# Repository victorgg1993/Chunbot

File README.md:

# 春 Bot

## Este proyecto tiene dos bloques:

### Mando

- **3D**: modelos 3D del mando
- **Codigo**: Ejemplos de código para el mando
- **PCB**: Diseños de la placa

### Robot

- **3D**: modelos 3D del robot
- **Codigo**: Ejemplos de código para el robot
- **PCB**: Diseños de la placa

## Instalación de dispositivos:

En Linux es necesario añadir los dispositivos en una whitelist en _/etc/udev/rules.d_. Se recomienda seguir la instalación oficial ya que las nuevas versiones de la IDE de Arduino lo gestionan de forma automática.

Link: https://docs.arduino.cc/software/ide-v2/tutorials/getting-started/ide-v2-downloading-and-installing/

---

## Instalación de las librerías:

Una vez se abra el menú, cargar las librerías que se encuentran en este proyecto.
La carpeta donde se encuentran las librerías a instalar es "LibreriasArduino".

---

## Elegir microcontrolador:

La flecha roja muestra en todo momento qué placa tenemos seleccionada, la verde indica qué puerto USB será usado para programar el microcontrolador.

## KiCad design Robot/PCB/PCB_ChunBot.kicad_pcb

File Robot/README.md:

# 春 Bot

## Contenido:

- PCB: Diseño de la PCB, tanto esquemáticos como la propia PCB ( Kicad )
- 3D: Modelos 3D ( FreeCAD )
- Codigo: Contiene códigos de ejemplo ( Arduino Mega 2560 )

## Pines:

|     Uso      | Pin |                                  Uso                                  |
| :----------: | :-: | :-------------------------------------------------------------------: |
|    Faros     | A14 |      Controla un mosfet que enciende y apaga los focos frontales      |
|              |     |                                                                       |
| Temperatura  | A15 |              Sensor de temperatura. Acepta TMP36 y LM35               |
|              |     |                                                                       |
|  Pulsadores  | A8  |                            Pulsador abajo                             |
|  Pulsadores  | A9  |                           Pulsador derecha                            |
|  Pulsadores  | A10 |                          Pulsador central/ok                          |
|  Pulsadores  | A11 |                          Pulsador izquierda                           |
|  Pulsadores  | A12 |                            Pulsador arriba                            |
|              |     |                                                                       |
|    Radio     | D18 |    Módulo radio NRF24L01, pin de interrupción. ( no implementado )    |
|    Radio     | D50 |                  Módulo radio NRF24L01, pin SPI MISO                  |
|    Radio     | D51 |                  Módulo radio NRF24L01, pin SPI MOSI                  |
|    Radio     | D52 |                  Módulo radio NRF24L01, pin SPI SCK                   |
|    Radio     | D53 |                  Módulo radio NRF24L01, pin SPI #CNS                  |
|    Radio     | D43 |                   Módulo radio NRF24L01, pin SPI CE                   |
|              |     |                                                                       |
| Siguelíneas  | D23 |           Sensor izquierdo exterior del seguidor de líneas            |
| Siguelíneas  | D41 |           Sensor izquierdo interior del seguidor de líneas            |
| Siguelíneas  | D42 |            Sensor derecho exterior del seguidor de líneas             |
| Siguelíneas  | D45 |            Sensor derecho interior del seguidor de líneas             |
|              |     |                                                                       |
| Display16x2  | D33 |                        Data 4 ( bus de datos )                        |
| Display16x2  | D35 |                        Data 5 ( bus de datos )                        |
| Display16x2  | D37 |                        Data 6 ( bus de datos )                        |
| Display16x2  | D39 |                        Data 7 ( bus de datos )                        |
| Display16x2  | D31 |                                Enable                                 |
| Display16x2  | D29 |                                  RS                                   |
| Display16x2  | D27 |      Controla un mosfet que enciende y apaga la luz del display       |
|              |     |                                                                       |
| Display7seg  | D17 |                              Segmento A                               |
| Display7seg  | D25 |                              Segmento B                               |
| Display7seg  | D16 |                              Segmento C                               |
| Display7seg  | D15 |                              Segmento D                               |
| Display7seg  | D14 |                              Segmento E                               |
| Display7seg  | D22 |                              Segmento F                               |
| Display7seg  | D24 |                              Segmento G                               |
|              |     |                                                                       |
|     OLED     | D20 |                   SDA, bus I2C de la pantalla OLED                    |
|     OLED     | D21 |                   SCL, bus I2C de la pantalla OLED                    |
|              |     |                                                                       |
|    Servos    | D8  |               Servo izquierdo. Usa PWM para su control                |
|    Servos    | D12 |                Servo derecho. Usa PWM para su control                 |
|    Servos    | D6  |                Servo extra 1. Usa PWM para su control                 |
|    Servos    | D7  |                Servo extra 2. Usa PWM para su control                 |
|    Servos    | D9  |                Servo extra 3. Usa PWM para su control                 |
|    Servos    | D10 |                Servo extra 4. Usa PWM para su control                 |
|    Servos    | D11 |                Servo extra 5. Usa PWM para su control                 |
|              |     |                                                                       |
|   Zumbador   | D5  |              Control vía PWM del zumbador piezoeléctrico              |
|              |     |                                                                       |
|   Mando TV   | D4  |     Sensor infrarrojo para el mando de TV. Usa el protocolo NEC32     |
|              |     |                                                                       |
| Ultrasonidos | D3  |          Emite una señal de eco que rebota contra el objeto           |
| Ultrasonidos | D2  | Recibe la señal de eco emitida por el otro pin ( usa interrupciones ) |
|              |     |                                                                       |

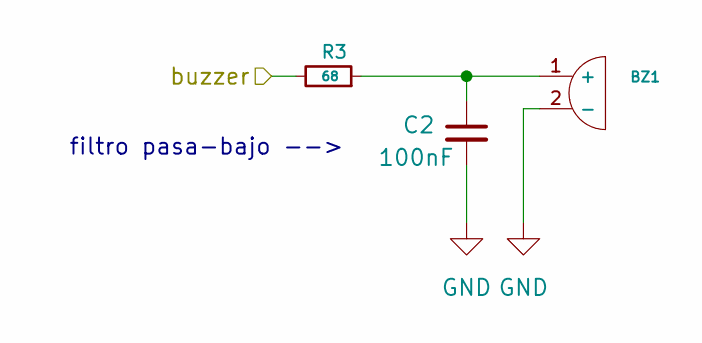
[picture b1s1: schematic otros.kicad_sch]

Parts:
BZ1: Buzzer_12x9.5RM7.6
C2: 100nF; C_0805_2012Metric_Pad1.18x1.45mm_HandSolder
R3: 68; R_0805_2012Metric

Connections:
GND: BZ1.2 (-), C2.2; also elsewhere on the board
unnamed: BZ1.1 (+), C2.1, R3.1
buzzer: R3.2; also elsewhere on the board

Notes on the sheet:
filtro pasa-bajo -->

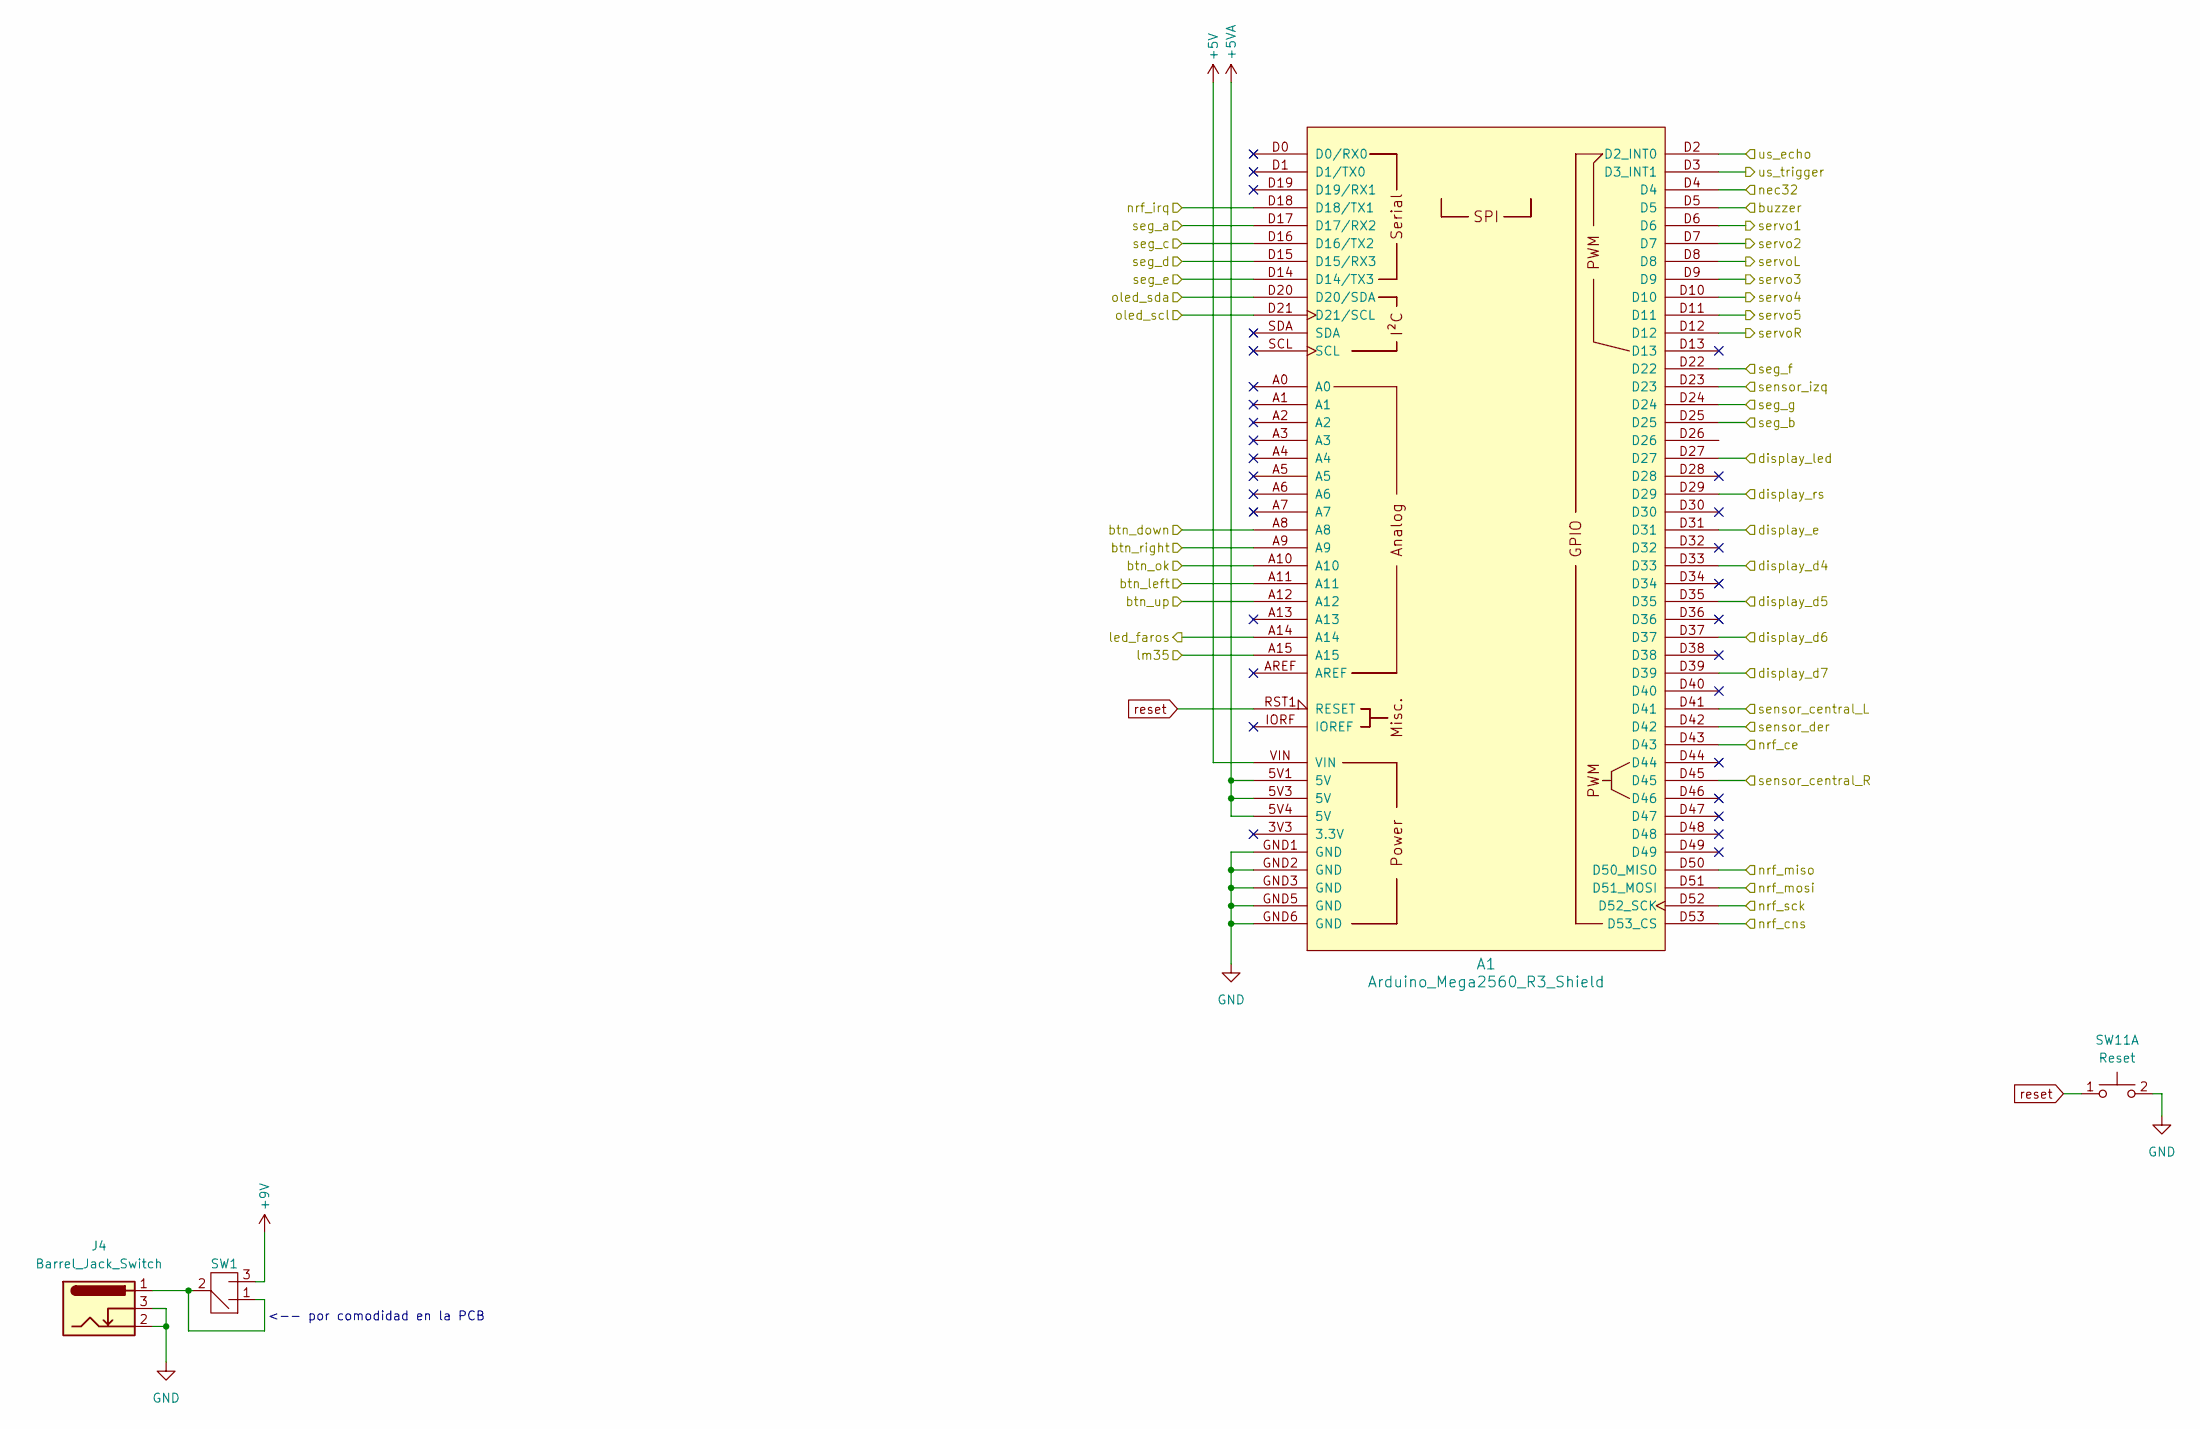
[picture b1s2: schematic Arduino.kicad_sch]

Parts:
A1: Arduino_Mega2560_R3_Shield
J4: Barrel_Jack_Switch; POWER_JACK_SLOT
SW1: SS12D10
SW11: Reset; SW_PUSH_6mm_H5mm

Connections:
+5V: A1.VIN; also elsewhere on the board
+5VA: A1.5V1 (5V), A1.5V3 (5V), A1.5V4 (5V); also elsewhere on the board
+9V: SW1.3; also elsewhere on the board
GND: A1.GND1 (GND), A1.GND2 (GND), A1.GND3 (GND), A1.GND5 (GND), A1.GND6 (GND), J4.2, J4.3, SW11.2 (D); also elsewhere on the board
unnamed: J4.1, SW1.1, SW1.2
btn_down: A1.A8; also elsewhere on the board
btn_left: A1.A11; also elsewhere on the board
btn_ok: A1.A10; also elsewhere on the board
btn_right: A1.A9; also elsewhere on the board
btn_up: A1.A12; also elsewhere on the board
buzzer: A1.D5; also elsewhere on the board
display_d4: A1.D33; also elsewhere on the board
display_d5: A1.D35; also elsewhere on the board
display_d6: A1.D37; also elsewhere on the board
display_d7: A1.D39; also elsewhere on the board
display_e: A1.D31; also elsewhere on the board
display_led: A1.D27; also elsewhere on the board
display_rs: A1.D29; also elsewhere on the board
led_faro: A1.A14; also elsewhere on the board
lm35: A1.A15; also elsewhere on the board
nec32: A1.D4; also elsewhere on the board
nrf_ce: A1.D43; also elsewhere on the board
nrf_cns: A1.D53 (D53_CS); also elsewhere on the board
nrf_irq: A1.D18 (D18/TX1); also elsewhere on the board
nrf_miso: A1.D50 (D50_MISO); also elsewhere on the board
nrf_mosi: A1.D51 (D51_MOSI); also elsewhere on the board
nrf_sck: A1.D52 (D52_SCK); also elsewhere on the board
oled_scl: A1.D21 (D21/SCL); also elsewhere on the board
oled_sda: A1.D20 (D20/SDA); also elsewhere on the board
reset: A1.RST1 (RESET), SW11.1 (C)
seg_a: A1.D17 (D17/RX2); also elsewhere on the board
seg_b: A1.D25; also elsewhere on the board
seg_c: A1.D16 (D16/TX2); also elsewhere on the board
seg_d: A1.D15 (D15/RX3); also elsewhere on the board
seg_e: A1.D14 (D14/TX3); also elsewhere on the board
seg_f: A1.D22; also elsewhere on the board
seg_g: A1.D24; also elsewhere on the board
sensor_central_L: A1.D41; also elsewhere on the board
sensor_central_R: A1.D45; also elsewhere on the board
sensor_der: A1.D42; also elsewhere on the board
sensor_izq: A1.D23; also elsewhere on the board
servo 1: A1.D6; also elsewhere on the board
servo 2: A1.D7; also elsewhere on the board
servo 3: A1.D9; also elsewhere on the board
servo 4: A1.D10; also elsewhere on the board
servo 5: A1.D11; also elsewhere on the board
servoL: A1.D8; also elsewhere on the board
servoR: A1.D12; also elsewhere on the board
ultrasonidos_echo: A1.D2 (D2_INT0); also elsewhere on the board
ultrasonidos_trigger: A1.D3 (D3_INT1); also elsewhere on the board

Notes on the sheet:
<-- por comodidad en la PCB

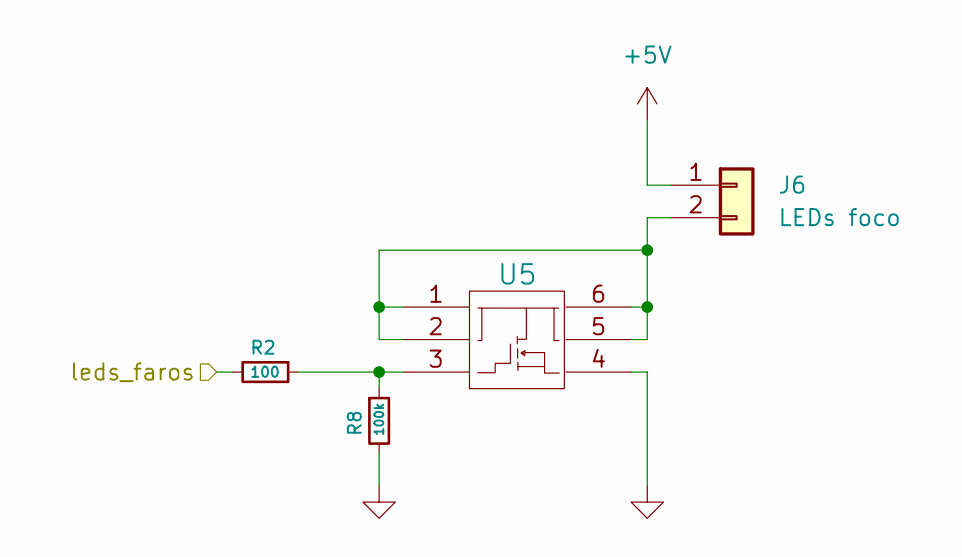
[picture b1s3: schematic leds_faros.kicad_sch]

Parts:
J6: LEDs foco; XH2.54_2Pin
R2: 100; R_0805_2012Metric
R8: 100k; R_0805_2012Metric
U5: SQ3456BEV; TSOP-6_1.65x3.05mm_P0.95mm

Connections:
+5V: J6.1; also elsewhere on the board
GND: R8.2, U5.4; also elsewhere on the board
unnamed: J6.2, U5.1, U5.2, U5.5, U5.6
unnamed: R2.1, R8.1, U5.3
led_faro: R2.2; also elsewhere on the board

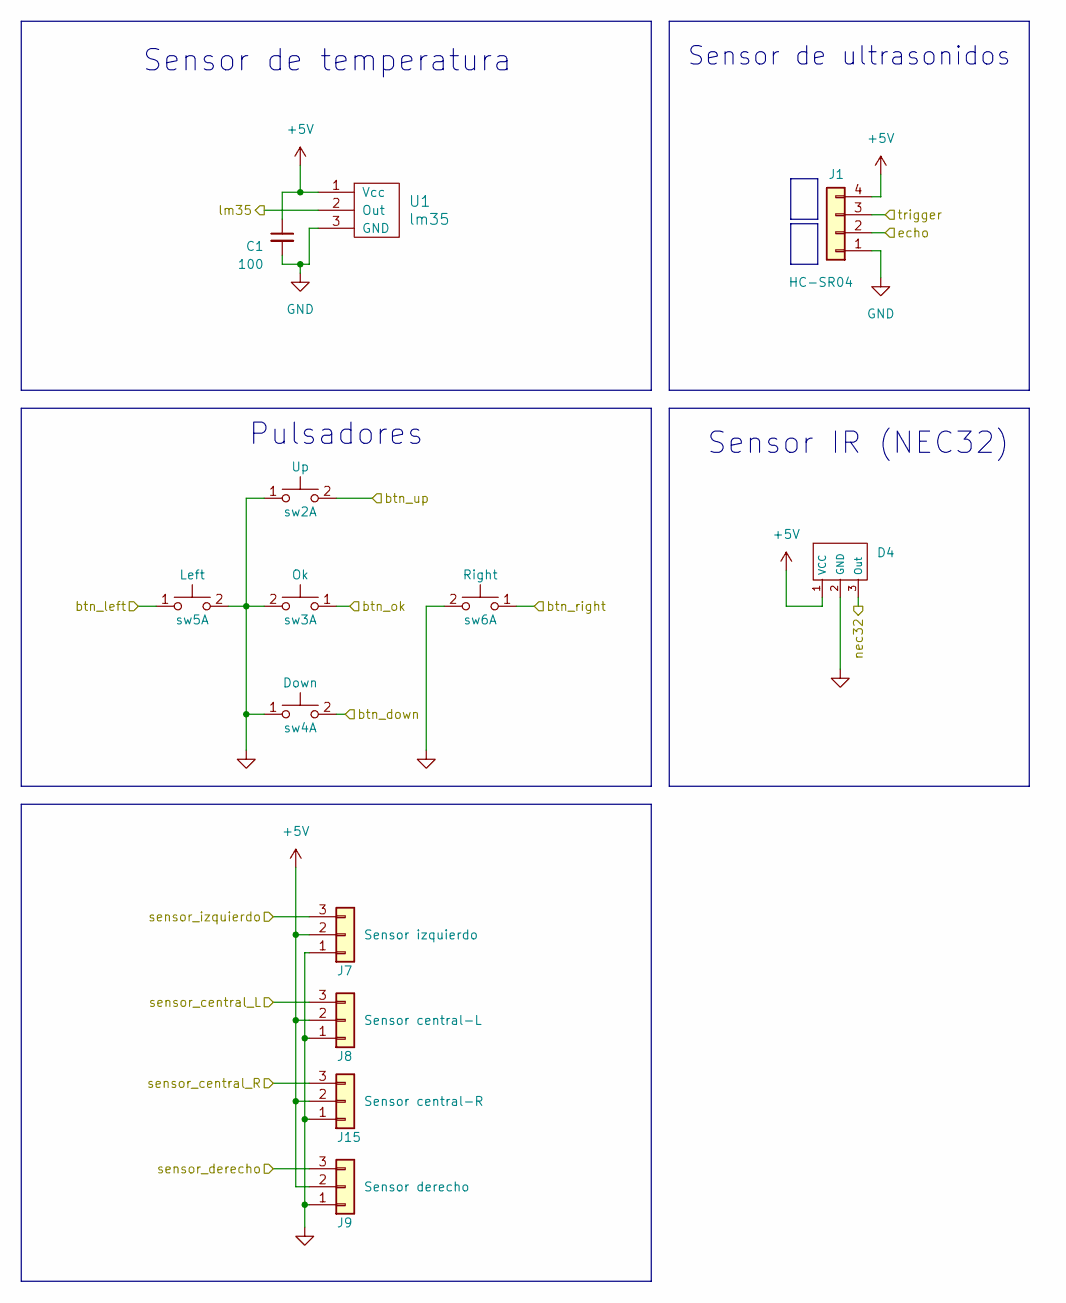
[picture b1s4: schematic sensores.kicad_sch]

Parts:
C1: 100; C_0805_2012Metric
D4: VS1838
J1: HC-SR04
J7: Sensor izquierdo; PinHeader_1x03_P2.54mm_Vertical
J8: Sensor central-L; PinHeader_1x03_P2.54mm_Vertical
J9: Sensor derecho; PinHeader_1x03_P2.54mm_Vertical
J15: Sensor central-R; PinHeader_1x03_P2.54mm_Vertical
U1: lm35; TO-92L_Inline_Wide
sw2: Up; SW_Push_1P1T_NO_CK_KSC7xxJ
sw3: Ok; SW_Push_1P1T_NO_CK_KSC7xxJ
sw4: Down; SW_Push_1P1T_NO_CK_KSC7xxJ
sw5: Left; SW_Push_1P1T_NO_CK_KSC7xxJ
sw6: Right; SW_Push_1P1T_NO_CK_KSC7xxJ

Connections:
+5V: C1.1, D4.1 (VCC), J1.4, J7.2, J8.2, J9.2, J15.2, U1.1 (Vcc); also elsewhere on the board
GND: C1.2, D4.2 (GND), J1.1, J7.1, J8.1, J9.1, J15.1, U1.3 (GND), sw2.1 (C), sw3.2 (D), sw4.1 (C), sw5.2 (D), sw6.2 (D); also elsewhere on the board
btn_down: sw4.2 (D); also elsewhere on the board
btn_left: sw5.1 (C); also elsewhere on the board
btn_ok: sw3.1 (C); also elsewhere on the board
btn_right: sw6.1 (C); also elsewhere on the board
btn_up: sw2.2 (D); also elsewhere on the board
lm35: U1.2 (Out); also elsewhere on the board
nec32: D4.3 (Out); also elsewhere on the board
sensor_central_L: J8.3; also elsewhere on the board
sensor_central_R: J15.3; also elsewhere on the board
sensor_der: J9.3; also elsewhere on the board
sensor_izq: J7.3; also elsewhere on the board
ultrasonidos_echo: J1.2; also elsewhere on the board
ultrasonidos_trigger: J1.3; also elsewhere on the board

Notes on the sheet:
Sensor IR (NEC32)
Sensor de ultrasonidos
Sensor de temperatura
Pulsadores

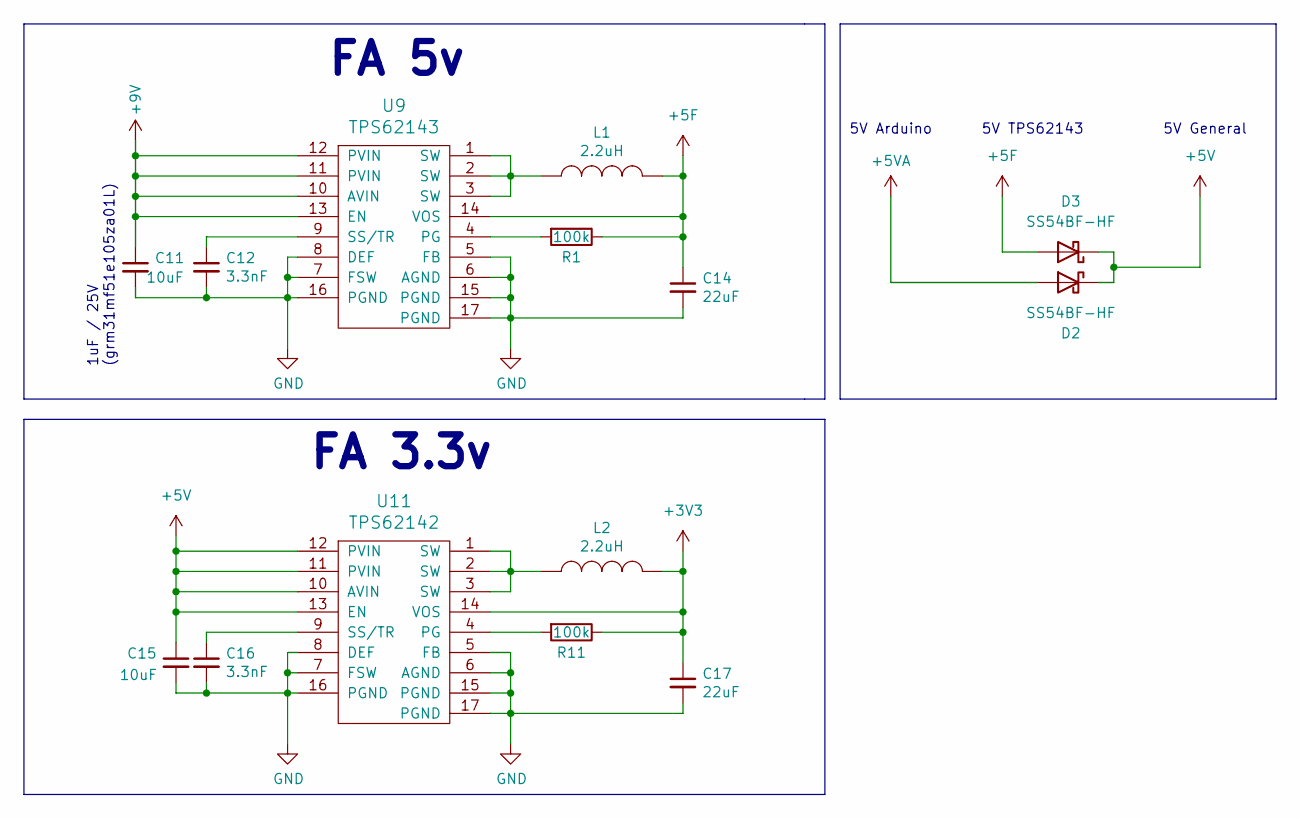
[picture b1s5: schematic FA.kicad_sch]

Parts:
C11: 10uF; C_1206_3216Metric_Pad1.33x1.80mm_HandSolder
C12, C16: 3.3nF; C_0805_2012Metric_Pad1.18x1.45mm_HandSolder
C14, C17: 22uF; C_0805_2012Metric_Pad1.18x1.45mm_HandSolder
C15: 10uF; C_0805_2012Metric_Pad1.18x1.45mm_HandSolder
D2, D3: SS54BF-HF; D_SMB_Handsoldering
L1, L2: 2.2uH; L_Taiyo-Yuden_NR-50xx_HandSoldering
R1, R11: 100k; R_0805_2012Metric_Pad1.20x1.40mm_HandSolder
U9: TPS62143; QFN-16-1EP_3x3mm_P0.5mm_EP1.7x1.7mm
U11: TPS62142; QFN-16-1EP_3x3mm_P0.5mm_EP1.7x1.7mm

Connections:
+3V3: C17.1, L2.2, R11.1, U11.14 (VOS); also elsewhere on the board
+5F: C14.1, D3.2 (A), L1.2, R1.1, U9.14 (VOS)
+5V: C15.1, D2.1 (K), D3.1 (K), U11.10 (AVIN), U11.11 (PVIN), U11.12 (PVIN), U11.13 (EN); also elsewhere on the board
+5VA: D2.2 (A); also elsewhere on the board
+9V: C11.1, U9.10 (AVIN), U9.11 (PVIN), U9.12 (PVIN), U9.13 (EN); also elsewhere on the board
GND: C11.2, C12.2, C14.2, C15.2, C16.2, C17.2, U9.5 (FB), U9.6 (AGND), U9.7 (FSW), U9.8 (DEF), U9.15 (PGND), U9.16 (PGND), U9.17 (PGND), U11.5 (FB), U11.6 (AGND), U11.7 (FSW), U11.8 (DEF), U11.15 (PGND), U11.16 (PGND), U11.17 (PGND); also elsewhere on the board
unnamed: L1.1, U9.1 (SW), U9.2 (SW), U9.3 (SW)
unnamed: L2.1, U11.1 (SW), U11.2 (SW), U11.3 (SW)
unnamed: R1.2, U9.4 (PG)
unnamed: C12.1, U9.9 (SS/TR)
unnamed: R11.2, U11.4 (PG)
unnamed: C16.1, U11.9 (SS/TR)

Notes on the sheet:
5V General
5V TPS62143
FA 5v
1uF / 25V (grm31mf51e105za01L)
5V Arduino
FA 3.3v

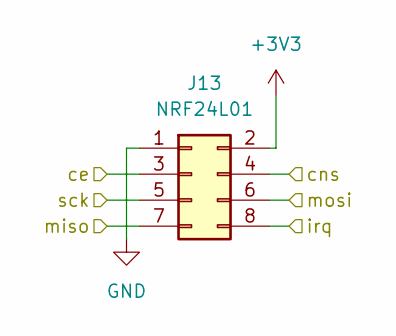
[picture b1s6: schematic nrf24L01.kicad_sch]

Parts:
J13: NRF24L01; PinHeader_2x04_P2.54mm_Vertical

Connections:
+3V3: J13.2; also elsewhere on the board
GND: J13.1; also elsewhere on the board
nrf_ce: J13.3; also elsewhere on the board
nrf_cns: J13.4; also elsewhere on the board
nrf_irq: J13.8; also elsewhere on the board
nrf_miso: J13.7; also elsewhere on the board
nrf_mosi: J13.6; also elsewhere on the board
nrf_sck: J13.5; also elsewhere on the board

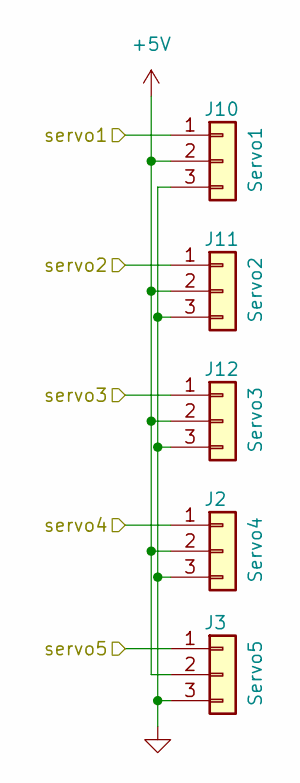
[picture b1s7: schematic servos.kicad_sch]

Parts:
J2: Servo4; PinHeader_1x03_P2.54mm_Vertical
J3: Servo5; PinHeader_1x03_P2.54mm_Vertical
J10: Servo1; PinHeader_1x03_P2.54mm_Vertical
J11: Servo2; PinHeader_1x03_P2.54mm_Vertical
J12: Servo3; PinHeader_1x03_P2.54mm_Vertical

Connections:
+5V: J2.2, J3.2, J10.2, J11.2, J12.2; also elsewhere on the board
GND: J2.3, J3.3, J10.3, J11.3, J12.3; also elsewhere on the board
servo 1: J10.1; also elsewhere on the board
servo 2: J11.1; also elsewhere on the board
servo 3: J12.1; also elsewhere on the board
servo 4: J2.1; also elsewhere on the board
servo 5: J3.1; also elsewhere on the board

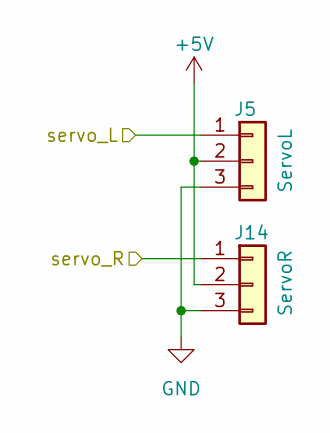
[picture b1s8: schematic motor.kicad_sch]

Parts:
J5: ServoL; PinHeader_1x03_P2.54mm_Horizontal
J14: ServoR; PinHeader_1x03_P2.54mm_Horizontal

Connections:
+5V: J5.2, J14.2; also elsewhere on the board
GND: J5.3, J14.3; also elsewhere on the board
servoL: J5.1; also elsewhere on the board
servoR: J14.1; also elsewhere on the board

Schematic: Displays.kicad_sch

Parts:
D1: SS511UBWA
DS1: WC1602A
R6: 200; R_0805_2012Metric
R7: 100; R_0805_2012Metric
R9: 100k; R_0805_2012Metric
R10: 150; R_0805_2012Metric
RV1: R_Potentiometer; 3362P
U2: OLED096
U3: SQ3456BEV; TSOP-6_1.65x3.05mm_P0.95mm

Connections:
+5V: DS1.2 (VDD), DS1.15 (LED(+)), RV1.1, U2.2 (VCC); also elsewhere on the board
GND: DS1.1 (VSS), DS1.5 (R/W), R9.2, R10.2, RV1.3, U2.1 (GND), U3.4; also elsewhere on the board
unnamed: D1.3 (K), D1.8 (K), R10.1
unnamed: DS1.16 (LED(-)), R6.1
unnamed: DS1.3 (VO), RV1.2
unnamed: R6.2, U3.1, U3.2, U3.5, U3.6
unnamed: R7.1, R9.1, U3.3
display_d4: DS1.11 (D4); also elsewhere on the board
display_d5: DS1.12 (D5); also elsewhere on the board
display_d6: DS1.13 (D6); also elsewhere on the board
display_d7: DS1.14 (D7); also elsewhere on the board
display_e: DS1.6 (E); also elsewhere on the board
display_led: R7.2; also elsewhere on the board
display_rs: DS1.4 (RS); also elsewhere on the board
oled_scl: U2.3 (SCL); also elsewhere on the board
oled_sda: U2.4 (SDA); also elsewhere on the board
seg_a: D1.7 (a); also elsewhere on the board
seg_b: D1.6 (b); also elsewhere on the board
seg_c: D1.4 (c); also elsewhere on the board
seg_d: D1.2 (d); also elsewhere on the board
seg_e: D1.1 (e); also elsewhere on the board
seg_f: D1.9 (f); also elsewhere on the board
seg_g: D1.10 (g); also elsewhere on the board

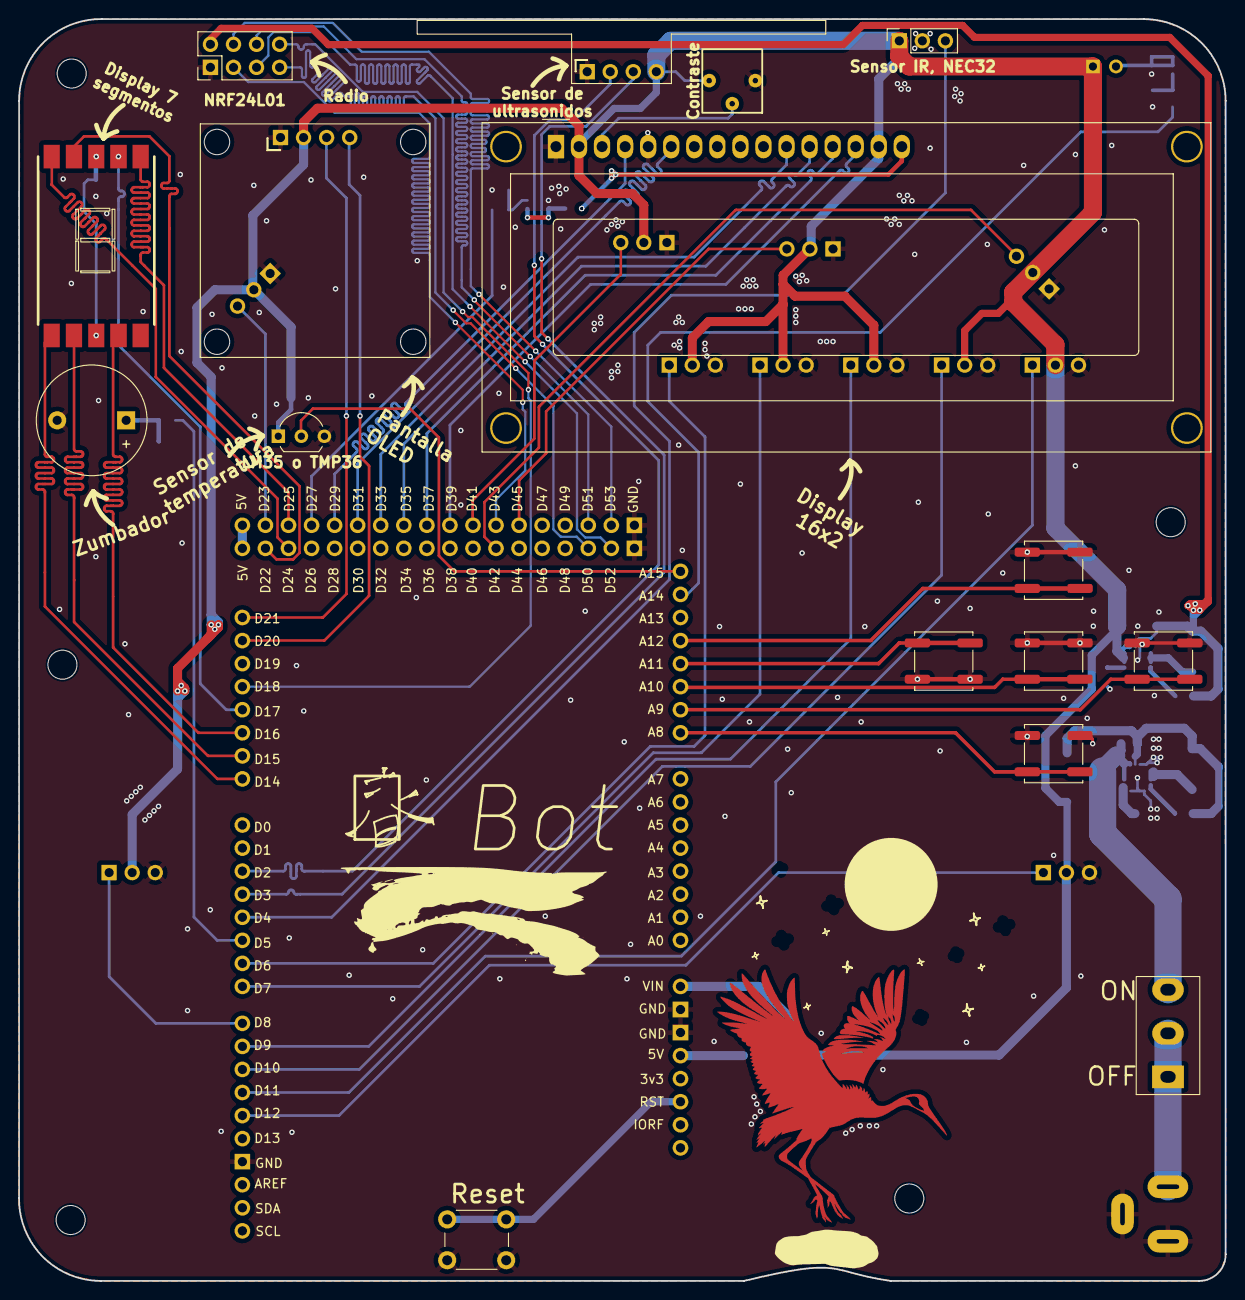
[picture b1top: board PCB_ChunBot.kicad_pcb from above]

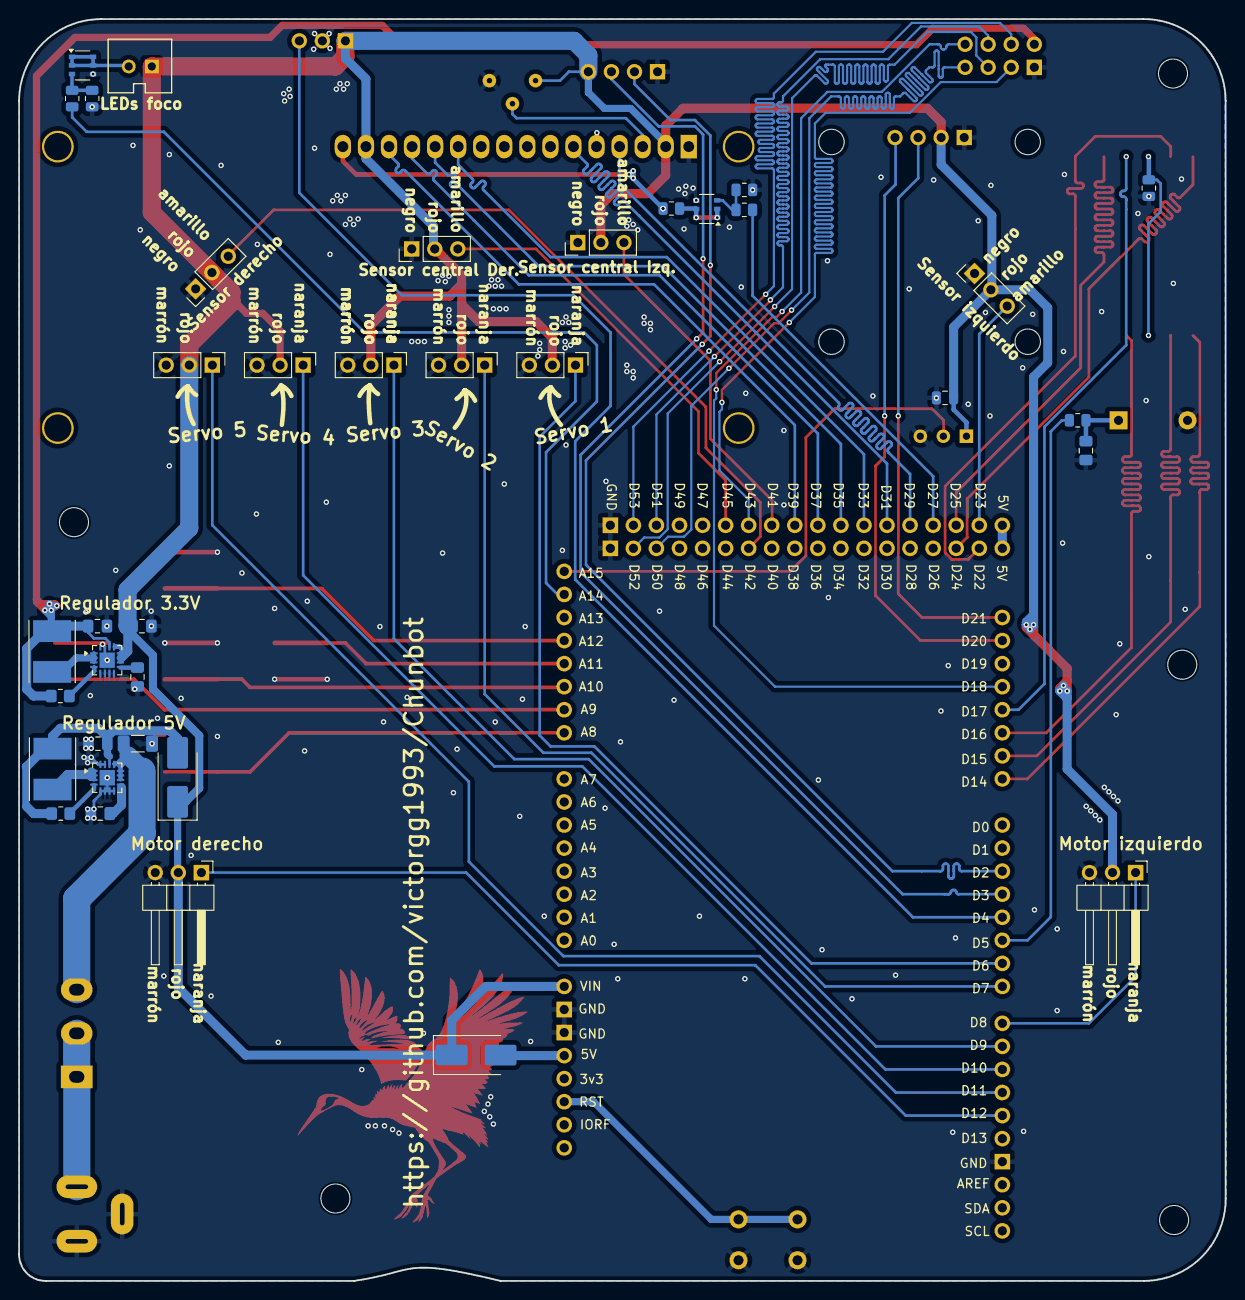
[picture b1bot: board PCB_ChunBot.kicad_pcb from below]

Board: 2 copper layers, 132.9 x 139.0 mm, 55 parts (38 on the bottom side), 66 nets.

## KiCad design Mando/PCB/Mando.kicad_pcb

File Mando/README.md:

# Mando 春 Bot

## Contenido:

- PCB: Diseño de la PCB, tanto esquemáticos como la propia PCB ( Kicad )
- 3D: Modelos 3D ( FreeCAD )
- Codigo: Contiene códigos de ejemplo ( Arduino Nano )

## Pines:

|      Uso      | Pin |                                  Uso                                  |
| :-----------: | :-: | :-------------------------------------------------------------------: |
| Interruptores | D5  |                      Interruptor lateral derecho                      |
| Interruptores | D6  |                     Interruptor lateral izquierdo                     |
|               |     |                                                                       |
|    Encoder    | D2  |                  Encoder, pin A. Usa interrupciones                   |
|    Encoder    | D3  |                  Encoder, pin B. Usa interrupciones                   |
|    Encoder    | D4  |                         Pulsador del encoder                          |
|               |     |                                                                       |
|   Zumbador    | A0  |            Pin PWM para el control del zumbador ( buzzer )            |
|               |     |                                                                       |
|   Joystick    | A4  | SDA chip ADC ( analogic to digital converter ) usado para el joystick |
|   Joystick    | A5  | SCL chip ADC ( analogic to digital converter ) usado para el joystick |
|   Joystick    | A6  |              alert pin del chip ADC ( no implementado )               |
|   Joystick    | D7  |                      Pulsador joystick izquierdo                      |
|   Joystick    | D8  |                       Pulsador joystick derecho                       |
|               |     |                                                                       |
|     OLED      | A4  |   SDA, bus I2C de la pantalla OLED. Pin compartido con el joystick    |
|     OLED      | A5  |   SCL, bus I2C de la pantalla OLED. Pin compartido con el joystick    |
|               |     |                                                                       |
|     Radio     | D13 |                  Módulo radio NRF24L01, pin SPI SCK                   |
|     Radio     | D12 |                  Módulo radio NRF24L01, pin SPI MISO                  |
|     Radio     | D11 |                  Módulo radio NRF24L01, pin SPI MOSI                  |
|     Radio     | D10 |                  Módulo radio NRF24L01, pin SPI #CNS                  |
|     Radio     | D9  |                   Módulo radio NRF24L01, pin SPI CE                   |
|               |     |                                                                       |

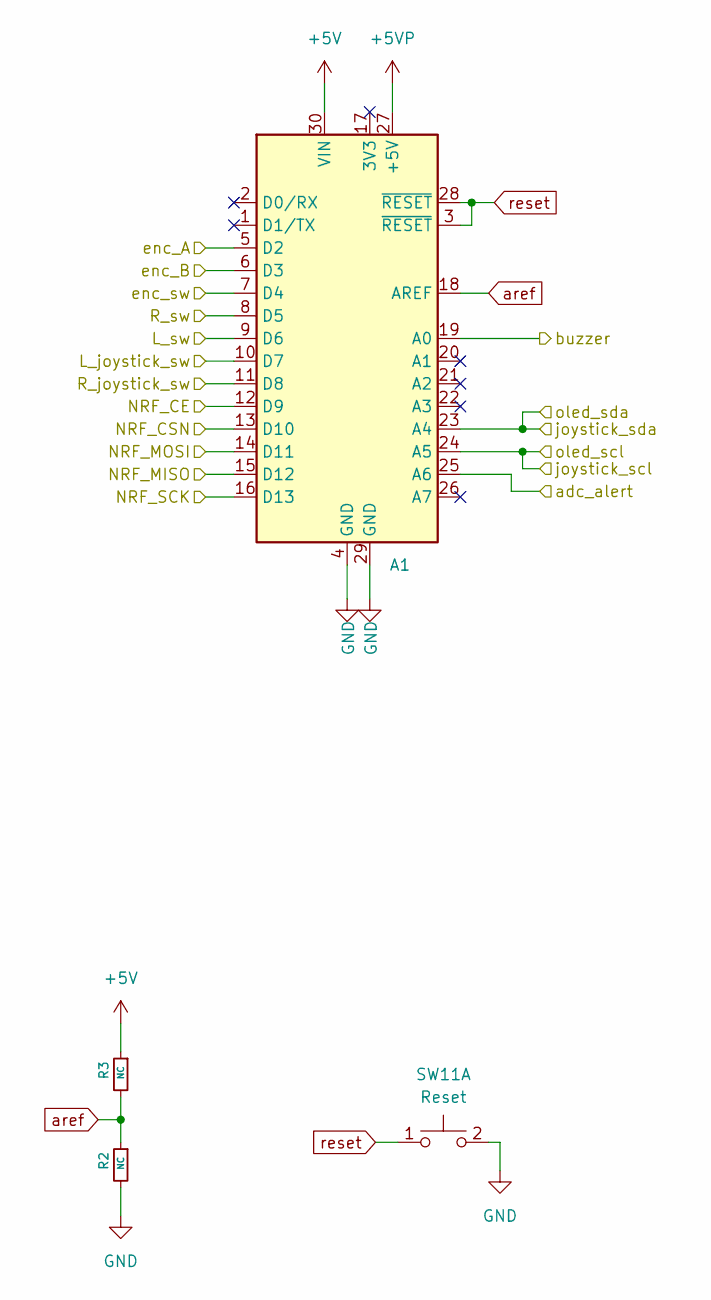
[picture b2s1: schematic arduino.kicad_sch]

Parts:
A1: Arduino_Nano_v3.x; Arduino_Nano
R2, R3: NC; R_0805_2012Metric
SW11: Reset; SW_Push_1P1T_NO_CK_KSC7xxJ

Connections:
+5V: A1.30 (VIN), R3.1; also elsewhere on the board
+5VP: A1.27 (+5V); also elsewhere on the board
GND: A1.4 (GND), A1.29 (GND), R2.2, SW11.2 (D); also elsewhere on the board
L_joy_sw: A1.10 (D7); also elsewhere on the board
L_switch: A1.9 (D6); also elsewhere on the board
adc_alert: A1.25 (A6); also elsewhere on the board
aref: A1.18 (AREF), R2.1, R3.2
buzzer: A1.19 (A0); also elsewhere on the board
enc_A: A1.5 (D2); also elsewhere on the board
enc_B: A1.6 (D3); also elsewhere on the board
enc_sw: A1.7 (D4); also elsewhere on the board
nrf_ce: A1.12 (D9); also elsewhere on the board
nrf_cns: A1.13 (D10); also elsewhere on the board
nrf_miso: A1.15 (D12); also elsewhere on the board
nrf_mosi: A1.14 (D11); also elsewhere on the board
nrf_sck: A1.16 (D13); also elsewhere on the board
oled_scl: A1.24 (A5); also elsewhere on the board
oled_sda: A1.23 (A4); also elsewhere on the board
r_joy_sw: A1.11 (D8); also elsewhere on the board
r_switch: A1.8 (D5); also elsewhere on the board
reset: A1.3 (~RESET), A1.28 (~RESET), SW11.1 (C)

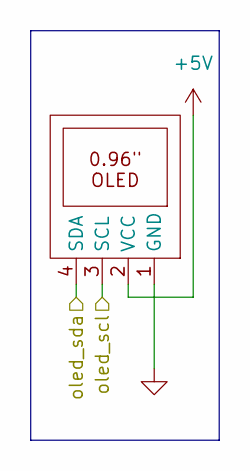
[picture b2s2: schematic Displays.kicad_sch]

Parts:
U3: OLED096

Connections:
+5V: U3.2 (VCC); also elsewhere on the board
GND: U3.1 (GND); also elsewhere on the board
oled_scl: U3.3 (SCL); also elsewhere on the board
oled_sda: U3.4 (SDA); also elsewhere on the board

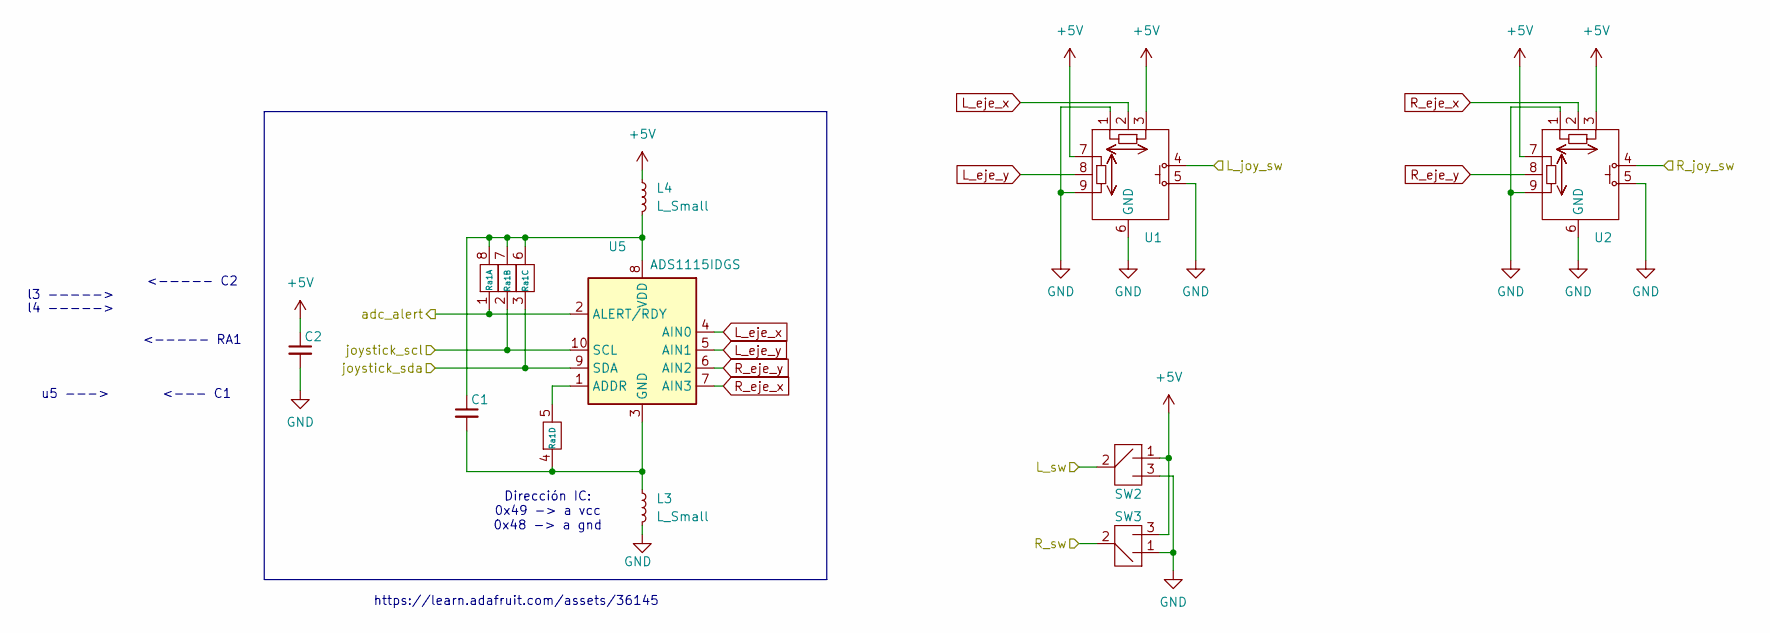
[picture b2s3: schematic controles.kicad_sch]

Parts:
C1, C2: C_Small; C_0805_2012Metric_Pad1.18x1.45mm_HandSolder
L3, L4: L_Small; L_0805_2012Metric_Pad1.05x1.20mm_HandSolder
Ra1: array_resistors_04; R_Array_Convex_4x0612
SW2, SW3: SS12D10_SMD
U1, U2: KY-023
U5: ADS1115IDGS; TSSOP-10_3x3mm_P0.5mm

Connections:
+5V: C2.1, L4.1, SW2.1, SW3.3, U1.3, U1.7, U2.3, U2.7; also elsewhere on the board
GND: C2.2, L3.2, SW2.3, SW3.1, U1.1, U1.5, U1.6 (GND), U1.9, U2.1, U2.5, U2.6 (GND), U2.9; also elsewhere on the board
L_eje_x: U1.2, U5.4 (AIN0)
L_eje_y: U1.8, U5.5 (AIN1)
L_joy_sw: U1.4; also elsewhere on the board
L_switch: SW2.2; also elsewhere on the board
unnamed: Ra1.5, U5.1 (ADDR)
unnamed: C1.2, L3.1, Ra1.4, U5.3 (GND)
unnamed: C1.1, L4.2, Ra1.6, Ra1.7, Ra1.8, U5.8 (VDD)
R_eje_x: U2.2, U5.7 (AIN3)
R_eje_y: U2.8, U5.6 (AIN2)
adc_alert: Ra1.1, U5.2 (ALERT/RDY); also elsewhere on the board
oled_scl: Ra1.2, U5.10 (SCL); also elsewhere on the board
oled_sda: Ra1.3, U5.9 (SDA); also elsewhere on the board
r_joy_sw: U2.4; also elsewhere on the board
r_switch: SW3.2; also elsewhere on the board

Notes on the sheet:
<----- C2
<----- RA1
https://learn.adafruit.com/assets/36145
Dirección IC: 0x49 -> a vcc 0x48 -> a gnd
u5 --->
l4 ----->
<--- C1
l3 ----->

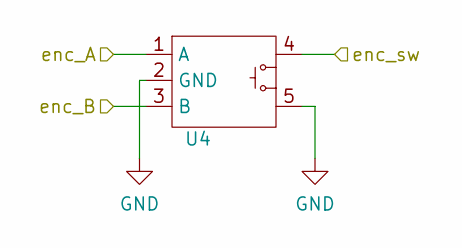
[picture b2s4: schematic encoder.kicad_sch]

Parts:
U4: EC11

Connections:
GND: U4.2 (GND), U4.5; also elsewhere on the board
enc_A: U4.1 (A); also elsewhere on the board
enc_B: U4.3 (B); also elsewhere on the board
enc_sw: U4.4; also elsewhere on the board
